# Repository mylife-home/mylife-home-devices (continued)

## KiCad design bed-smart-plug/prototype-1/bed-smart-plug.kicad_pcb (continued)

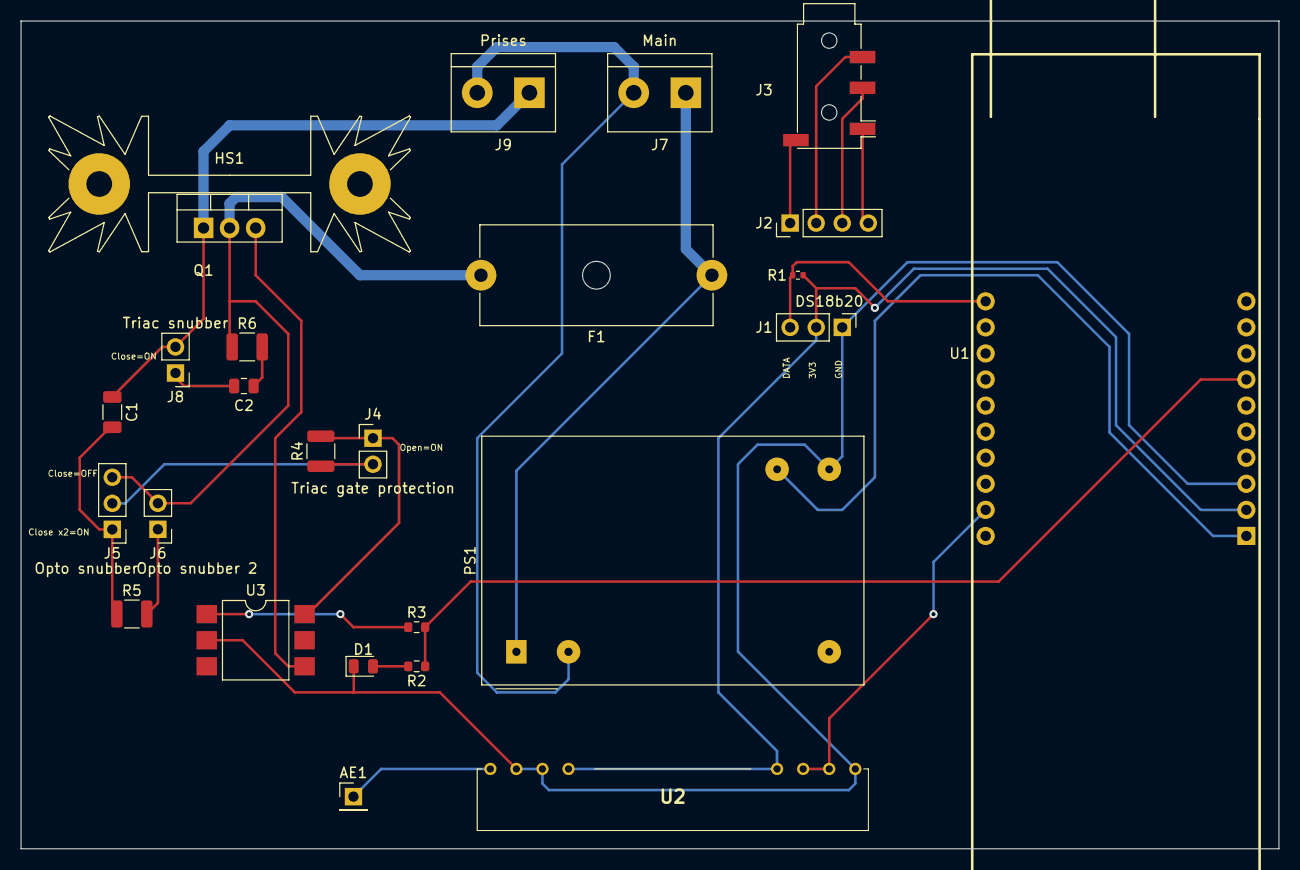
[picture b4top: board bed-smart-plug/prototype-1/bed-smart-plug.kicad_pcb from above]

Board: 2 copper layers, 122.6 x 80.6 mm, 26 parts (0 on the bottom side), 24 nets.

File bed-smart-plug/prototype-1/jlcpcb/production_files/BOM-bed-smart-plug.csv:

Comment,Designator,Footprint,LCSC
10nF/400V,C2,C_0805_2012Metric,C106840
MOC3021M,U3,SMDIP-6_W9.53mm,C108500
220Ω,"R2,R3",R_0603_1608Metric,C22962
LED,D1,D_0805_2012Metric,C2297
4.7KΩ,R1,R_0402_1005Metric,C25900
360Ω/0.5W,R4,R_1210_3225Metric,C2759574
47nF/400V,C1,C_1206_3216Metric,C309031
39Ω/0.5W,R6,R_1210_3225Metric,C422307
3.5mm headphone jack,J3,Jack_3.5mm_PJ320D_Horizontal,C521460
470Ω/0.5W,R5,R_1210_3225Metric,C830186
Conn_01x02_Male,J2,PinHeader_1x04_P2.54mm_Vertical,
Prises,J9,TerminalBlock_bornier-2_P5.08mm,
Triac snubber,J8,PinHeader_1x02_P2.54mm_Vertical,
AM-RX12A-433P,U2,AMRX12A433P,
Opto snubber 2,J6,PinHeader_1x02_P2.54mm_Vertical,
Antenna,AE1,PinHeader_1x01_P2.54mm_Vertical,
Heatsink,HS1,Heatsink_Fischer_SK104-STC-STIC_35x13mm_2xDrill2.5mm,
DS18b20,J1,PinHeader_1x03_P2.54mm_Vertical,
Alim RS PRO 5V 1A,PS1,Converter_ACDC_MeanWell_IRM-03-xx_THT,
ESP32-POE,U1,ESP32-POE,
BT136-600E,Q1,TO-220-3_Vertical,
Opto snubber,J5,PinHeader_1x03_P2.54mm_Vertical,
3A,F1,Fuseholder_Cylinder-5x20mm_Schurter_0031_8201_Horizontal_Open,
Triac gate protection,J4,PinHeader_1x02_P2.54mm_Vertical,
Main,J7,TerminalBlock_bornier-2_P5.08mm,

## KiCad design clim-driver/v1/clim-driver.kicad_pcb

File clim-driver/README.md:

# Clim driver

## Besoin

- Wifi
- doit tenir dans le boitier de clim directement
- alimenté par la clim
- le plus de contrôle possible
- ajouter un capteur de température

### Info clim

- RDC: Toshiba air conditioner RAS-13BKV-E1
- R1: 4x Toshiba air conditioner RAS-05BKV-E
- Telecommande : Toshiba WH-UA01NE
- place derriere capot : 70x15x25
- place pompe relevage :
  - https://www.manomano.fr/p/pompe-relevage-climatisation-mini-orange-230v-aspen-3124579
  - 39x34x80, prévoir sortie cable dans facade 39x34

## Design

- IR send/recv :
  - https://www.wemos.cc/en/latest/_static/files/sch_ir_v1.0.0.pdf
  - https://www.wemos.cc/en/latest/d1_mini_shield/ir.html
  - Led IR: https://fr.rs-online.com/web/p/leds-infrarouges/6997708
  - 18ohm @ 3.3v
- Temp : DS18B2 :
  - en dehors du boitier sinon la temp sera faussée avec la chaleur de l'ESP8266
- Wemos D1 mini :
  - https://www.amazon.fr/dp/B093G72SHN
  - 34x26
- Alim :
  - alim 220v -> 5V 1A : https://fr.rs-online.com/web/p/alimentations-a-decoupage/1812200
  - 37 x 24.5 x 18
  - apparemment il n'existe pas plus petit
- Boitier :
  - https://fr.rs-online.com/web/p/boitiers-pour-usage-general/9190373

## V1

### Wiring

### 3D view

### Main

### Images

| | | |
|---|---|---|
||||
||||

#### CH1

_(pas d'image)_

#### CH2

| | | |
|---|---|---|
||||

#### CH3

| | | |
|---|---|---|
||||

#### CHP

_(pas d'image)_

#### RDC

| | | |
|---|---|---|
||||

### Notes

- Sertissage Dupont : dénuder sur 5mm et ne sertir que le fil conducteur pas la gaine
- Agrandir le trou du boitier à la perceuse à colonne avant de mettre le pas de vis
- Couleurs cable led
  - blanc = +
  - bleu = -
- Couleurs cable DS18B20
  - jaune = IN
  - rouge = 3V3
  - noir = GND

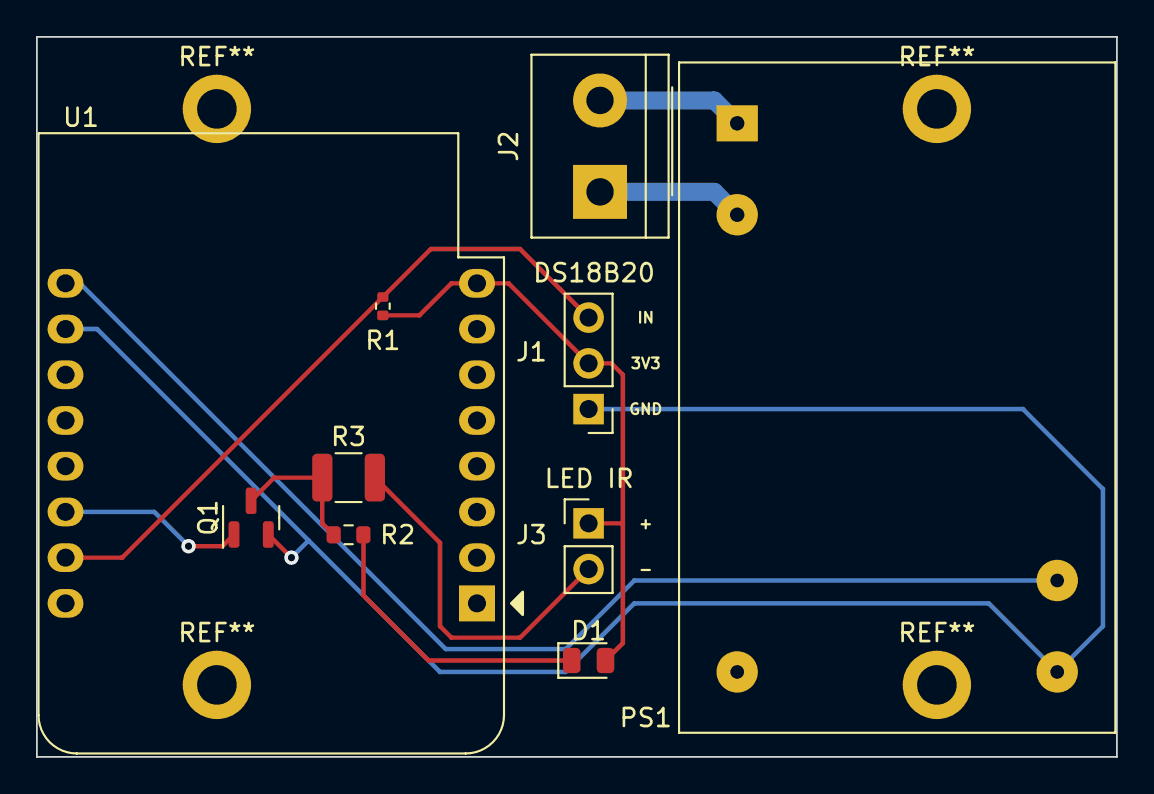
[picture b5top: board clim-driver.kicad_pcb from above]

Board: 2 copper layers, 60.0 x 40.0 mm, 10 parts (0 on the bottom side), 10 nets.

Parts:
D1: LED; D_0805_2012Metric
J1: Conn_01x03_Male; PinHeader_1x03_P2.54mm_Vertical
J2: Screw_Terminal_01x02; TerminalBlock_bornier-2_P5.08mm
J3: Conn_01x02_Pin; PinHeader_1x02_P2.54mm_Vertical
PS1: Alim RS PRO 5V 1A; Converter_ACDC_MeanWell_IRM-03-xx_THT
Q1: BSS138; SOT-23
R1: 4.7KΩ; R_0402_1005Metric
R2: 1KΩ; R_0603_1608Metric
R3: 18Ω/0.5W; R_1210_3225Metric
U1: WeMos_D1_mini; WEMOS_D1_mini_light

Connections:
+3V3: D1.2 (A), J1.2, J3.1, R1.1, U1.8 (3V3)
+5V: PS1.16 (+Vo), U1.9 (5V)
GND: J1.1, PS1.14 (-Vo), Q1.2 (S), U1.10 (GND)
LINE: J2.2, PS1.1 (AC/L)
NEUT: J2.1, PS1.3 (AC/N)
unnamed: D1.1 (K), R2.2
unnamed: J1.3, R1.2, U1.15 (RX)
unnamed: J3.2, R3.2
unnamed: Q1.3 (D), R2.1, R3.1
unnamed: Q1.1 (G), U1.14 (SCL/D1)

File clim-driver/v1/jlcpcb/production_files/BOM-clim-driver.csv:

Comment,Designator,Footprint,LCSC
1KΩ,R2,R_0603_1608Metric,C21190
LED,D1,D_0805_2012Metric,C2297
4.7KΩ,R1,R_0402_1005Metric,C25900
BSS138,Q1,SOT-23,C2938375
18Ω/0.5W,R3,R_1210_3225Metric,C333138
Conn_01x03_Male,J1,PinHeader_1x03_P2.54mm_Vertical,
Screw_Terminal_01x02,J2,TerminalBlock_bornier-2_P5.08mm,
WeMos_D1_mini,U1,WEMOS_D1_mini_light,
Conn_01x02_Pin,J3,PinHeader_1x02_P2.54mm_Vertical,
Alim RS PRO 5V 1A,PS1,Converter_ACDC_MeanWell_IRM-03-xx_THT,

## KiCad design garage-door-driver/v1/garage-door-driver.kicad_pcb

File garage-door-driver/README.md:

# Garage door driver

## Besoin

- doit tenir dans le boitier de la porte ou a côté avec un cable de commande qui sort du boitier
- Wifi
- alimenté par l'alim de la porte
- le plus de contrôle possible
- ajouter un capteur de température

### Fonctionnement de la porte

- Documentation:
  https://www.tubauto.fr/app/uploads/2018/02/procom7-3-fr.pdf

- Moteur garage:

| | | |
|---|---|---|
||||
||||

- Notes:
  - 4 borniers à gauche (comme matériel HiFi)
    - 2 à gauche : alimentation 13V
    - 2 à droite : poussoir déclencheur externe (24v)
  - 2 borniers noirs
    - Sortie (relais d'option) (24v)
      réglage DIL A=OFF B=ON => fin de course (signal ON si porte fermée, OFF sinon)
  - 4 borniers à droite
    - de gauche à droite : 20 - 21 - 5 - 23
    - 20 commun
    - 21-20 => poussoir ouverture totale (4.8v)
    - 5-20 alimentation 24v
    - 23-20 => poussoir ouverture partielle (4.8v)
  - Alimentation moteur:
    - +24v quand montée
    - -24v quand descente

## Design

- Board
  - Wemos D1 mini (ESP8266) 
  - https://amzn.eu/d/irlLEVS
- Alim
  - connexion au 24v
  - https://fr.rs-online.com/web/p/regulateurs-a-decoupage/1934004
  - regarder datasheet pour condensateurs à rajouter
- Borniers
  - https://fr.rs-online.com/web/p/borniers-pour-circuits-imprimes/7901098
- outputs x2 (ouverture partielle/totale)
  - 4.8v vers un commun qui semble etre GND, semble parfait pour sortie transistor
  - 4n35 (1.3v 10ma) https://fr.farnell.com/vishay/4n35/optocoupleur-phototransistor-5000vrms/dp/1328375
  - GPIO 3.3v => R=220ohm
- inputs x3 (moteur double sens, relais d'option)
  - 24v
  - 4n35 (1.3v 10ma) https://fr.farnell.com/vishay/4n35/optocoupleur-phototransistor-5000vrms/dp/1328375
  - 24v => R=2.2kohm
- fixation/layout PCB
  - PCB avec pin header (1 pin sur 2 pour pas de 5.08)
  - les pins headers sont serrés dans les 4 borniers à droite
  - prévoir borniers + fils pour les 2 borniers du milieu
  - taille
    - pin headers vers bord 2.54mm
    - pin headers vers dégagement 1.5cm
    - bord droit retrait degradé sur 1 cm
    - Épaisseur PCB ok des 2 côtés (hauteur/profondeur)
    - H totale = 5cm
    - L totale = 9.5cm

## V1

### Wiring

- GPIO14 - D5 : in moteur (active low)
- GPIO12 - D6 : in moteur (active low)
- GPIO13 - D7 : in porte fermée (active low)
- GPIO4 - D2 : out ouverture partielle
- GPIO5 - D1 : out ouverture totale
- GPIO3 - RX : DS18B20

### 3D view

### Main

### Images

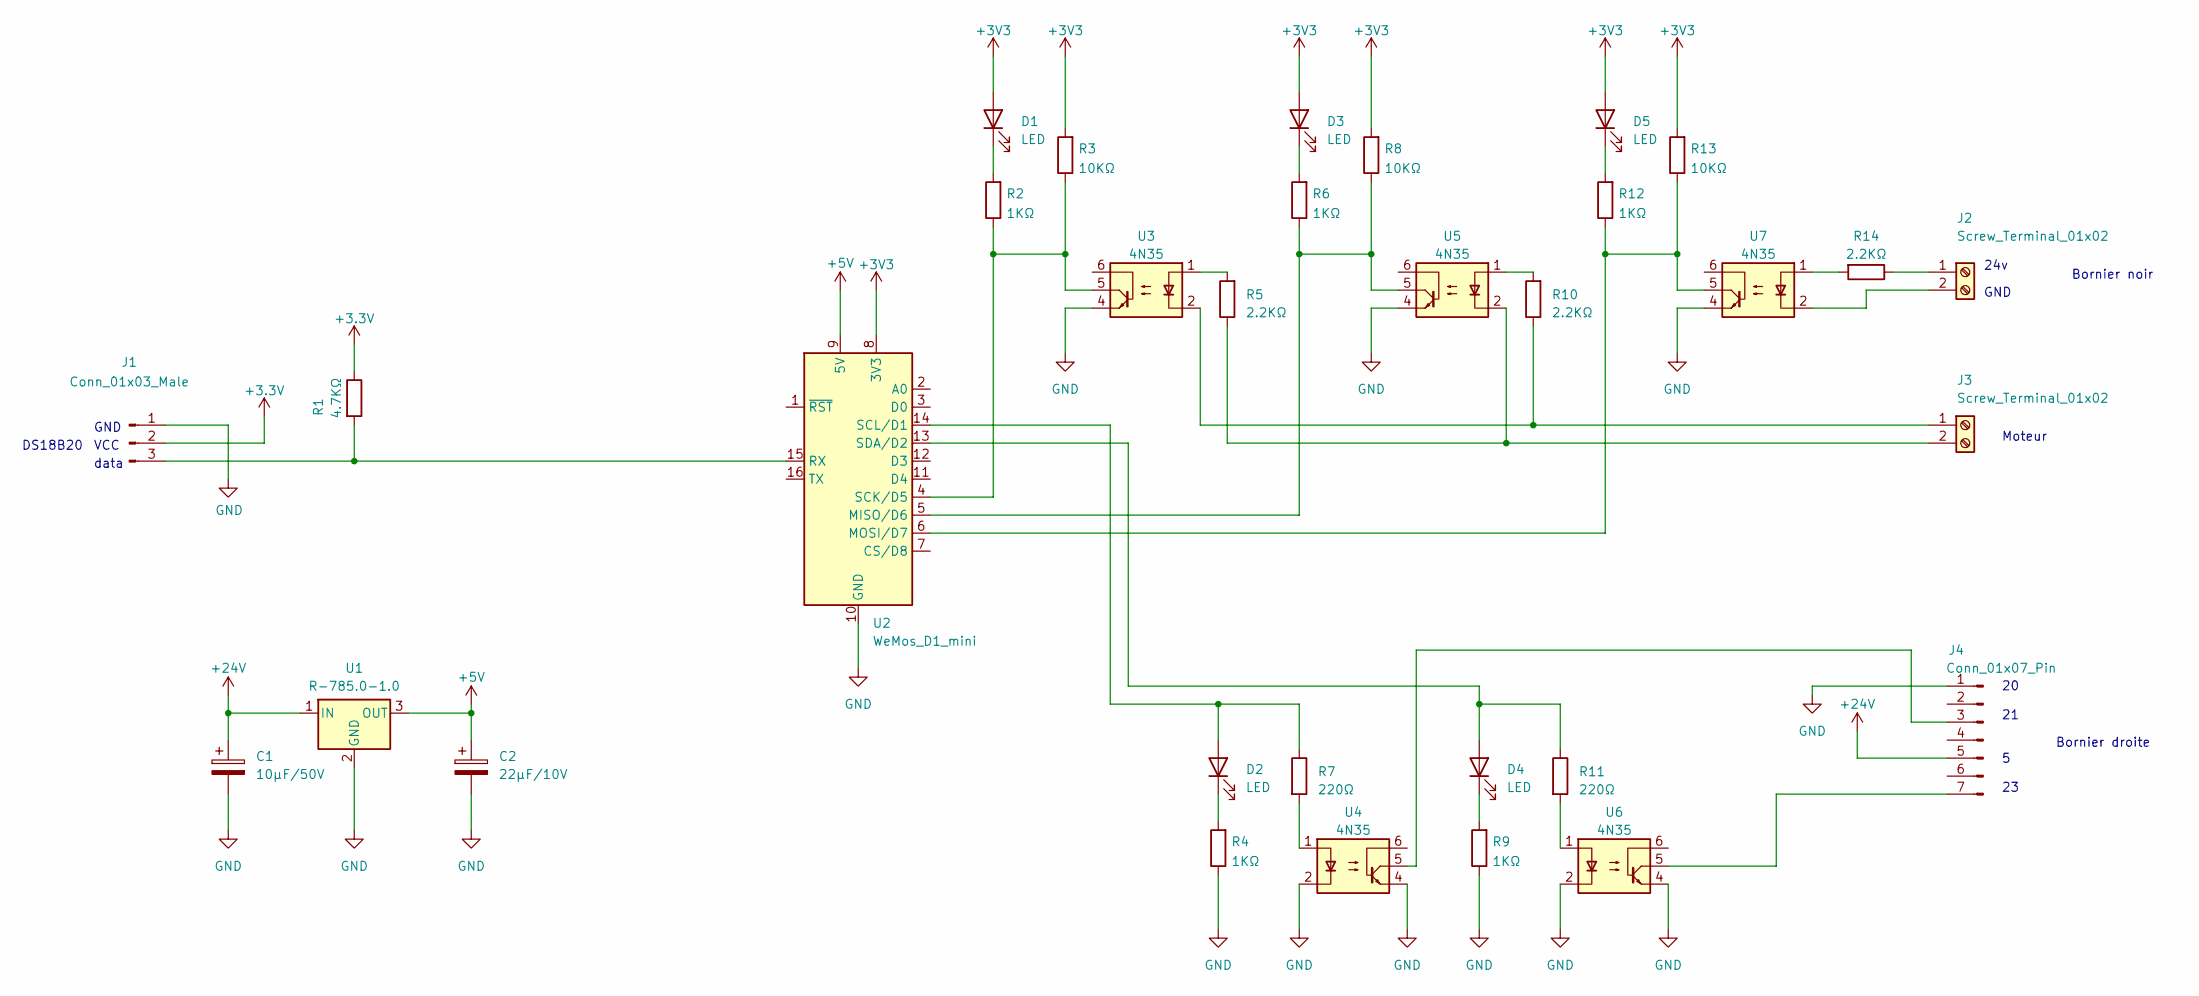
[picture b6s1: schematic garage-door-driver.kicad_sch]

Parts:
C1: 10μF/50V; C_1206_3216Metric; LCSC C417124
C2: 22μF/10V; C_0805_2012Metric; LCSC C92814
D1, D2, D3, D4, D5: LED; D_0805_2012Metric; LCSC C2297
J1: Conn_01x03_Male; PinHeader_1x03_P2.54mm_Vertical
J2, J3: Screw_Terminal_01x02; RS PRO Terminal Small x2
J4: Conn_01x07_Pin; PinHeader_1x07_P2.54mm_Vertical
R1: 4.7KΩ; R_0402_1005Metric; LCSC C25900
R2, R4, R6, R9, R12: 1KΩ; R_0603_1608Metric; LCSC C21190
R3, R8, R13: 10KΩ; R_0603_1608Metric; LCSC C25804
R5, R10, R14: 2.2KΩ; R_0603_1608Metric; LCSC C176136
R7, R11: 220Ω; R_0603_1608Metric; LCSC C22962
U1: R-785.0-1.0; Converter_DCDC_RECOM_R-78E-0.5_THT
U2: WeMos_D1_mini; WEMOS_D1_mini_light
U3, U4, U5, U6, U7: 4N35; DIP-6_W8.89mm_SMDSocket_LongPads; LCSC C500385

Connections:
+5V: C2.1, U1.3 (OUT), U2.9 (5V)
+24V: C1.1, J4.5, U1.1 (IN)
GND: C1.2, C2.2, J1.1, J4.1, R4.1, R9.1, U1.2 (GND), U2.10 (GND), U3.4, U4.2, U4.4, U5.4, U6.2, U6.4, U7.4
unnamed: D1.1 (K), R2.2
unnamed: D2.2 (A), R7.1, U2.14 (SCL/D1)
unnamed: D2.1 (K), R4.2
unnamed: D3.1 (K), R6.2
unnamed: D4.2 (A), R11.1, U2.13 (SDA/D2)
unnamed: D4.1 (K), R9.2
unnamed: D5.1 (K), R12.2
unnamed: J1.3, R1.2, U2.15 (RX)
unnamed: J2.1, R14.1
unnamed: J2.2, U7.2
unnamed: J3.1, R10.1, U3.2
unnamed: J3.2, R5.1, U5.2
unnamed: J4.3, U4.5
unnamed: J4.7, U6.5
unnamed: R5.2, U3.1
unnamed: R7.2, U4.1
unnamed: R10.2, U5.1
unnamed: R11.2, U6.1
unnamed: R14.2, U7.1
unnamed: R6.1, R8.1, U2.5 (MISO/D6), U5.5
unnamed: R12.1, R13.1, U2.6 (MOSI/D7), U7.5
unnamed: R2.1, R3.1, U2.4 (SCK/D5), U3.5

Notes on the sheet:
Bornier droite
20 21 5 23
GND
Bornier noir
24v
data
VCC
Moteur
DS18B20

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
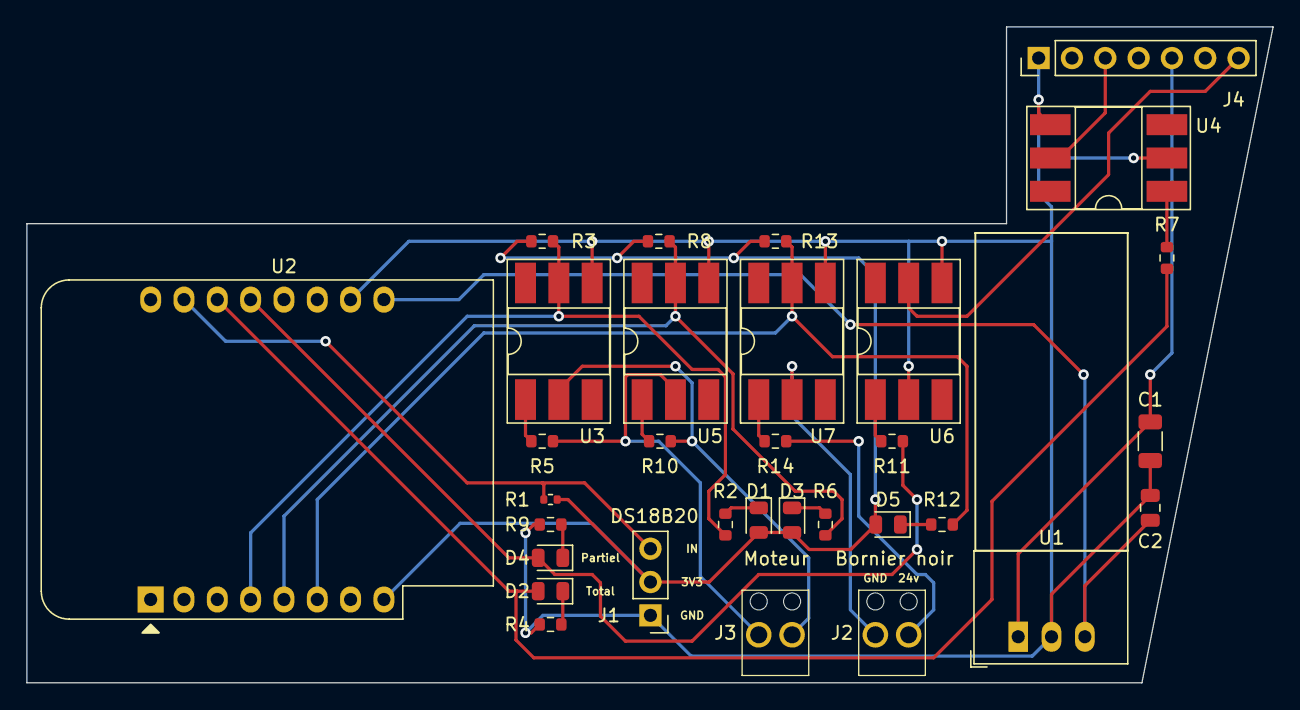
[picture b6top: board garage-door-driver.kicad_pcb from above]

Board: 2 copper layers, 95.0 x 50.0 mm, 32 parts (0 on the bottom side), 26 nets.

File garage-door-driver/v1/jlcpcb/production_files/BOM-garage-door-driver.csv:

Comment,Designator,Footprint,LCSC
2.2KΩ,"R10,R14,R5",R_0603_1608Metric,C176136
1KΩ,"R12,R2,R4,R6,R9",R_0603_1608Metric,C21190
220Ω,"R11,R7",R_0603_1608Metric,C22962
LED,"D1,D2,D3,D4,D5",D_0805_2012Metric,C2297
10KΩ,"R13,R3,R8",R_0603_1608Metric,C25804
4.7KΩ,R1,R_0402_1005Metric,C25900
10μF/50V,C1,C_1206_3216Metric,C417124
4N35,"U3,U4,U5,U6,U7",DIP-6_W8.89mm_SMDSocket_LongPads,C500385
22μF/10V,C2,C_0805_2012Metric,C92814
Conn_01x03_Male,J1,PinHeader_1x03_P2.54mm_Vertical,
WeMos_D1_mini,U2,WEMOS_D1_mini_light,
Conn_01x07_Pin,J4,PinHeader_1x07_P2.54mm_Vertical,
Screw_Terminal_01x02,J2,RS PRO Terminal Small x2,
R-785.0-1.0,U1,Converter_DCDC_RECOM_R-78E-0.5_THT,
Screw_Terminal_01x02,J3,RS PRO Terminal Small x2,

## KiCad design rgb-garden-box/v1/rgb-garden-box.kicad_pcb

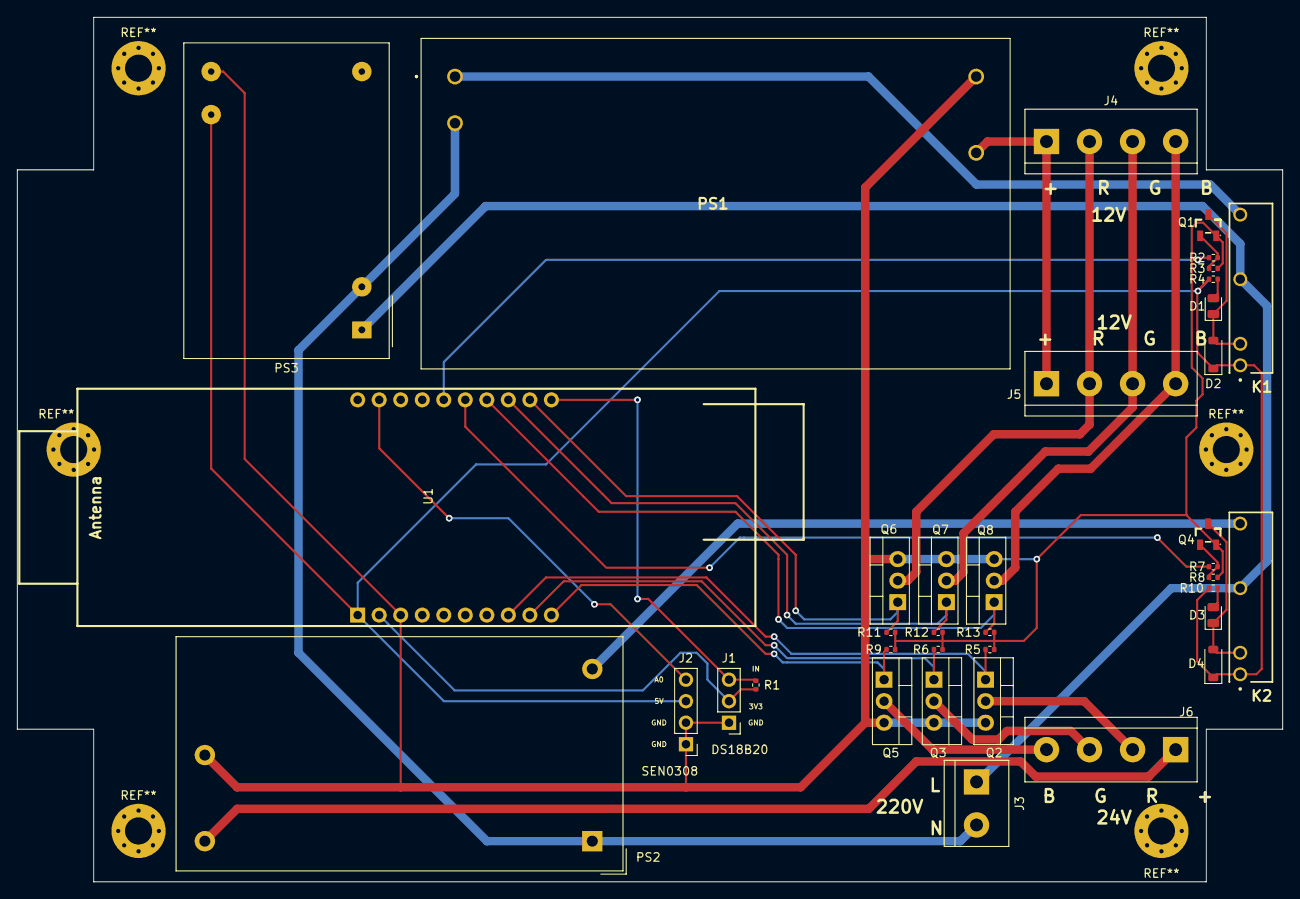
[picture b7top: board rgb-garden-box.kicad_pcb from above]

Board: 2 copper layers, 149.3 x 102.0 mm, 37 parts (0 on the bottom side), 31 nets.

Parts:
D1, D3: LED; D_0805_2012Metric
D2, D4: 1N4148; D_SOD-123
J1: Conn_01x03_Male; PinHeader_1x03_P2.54mm_Vertical
J2: Conn_01x04_Male; PinHeader_1x04_P2.54mm_Vertical
J3: Screw_Terminal_01x02; TerminalBlock_bornier-2_P5.08mm
J4, J5, J6: Screw_Terminal_01x04; TerminalBlock_bornier-4_P5.08mm
K1, K2: G6DN-1A-L_DC5; G6DN-1A-L
PS1: Mean Well 12V 2.5A (30W); IRM-30-12
PS2: RS PRO 24V 833mA (20W); RS PRO Alim 5V 2A
PS3: Alim RS PRO 5V 1A; Converter_ACDC_MeanWell_IRM-03-xx_THT
Q1, Q4: 2N3904; SOT-23-3_L2.9-W1.3-P1.90-LS2.4-TR
Q2, Q3, Q5, Q6, Q7, Q8: IRLZ44N; TO-220-3_Vertical
R1: 4.7KΩ; R_0402_1005Metric
R2, R4, R7, R10: 1KΩ; R_0402_1005Metric
R3, R5, R6, R8, R9, R11, R12, R13: 10KΩ; R_0402_1005Metric
U1: ESP32-POE

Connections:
+3V3: J1.2, R1.1, U1.2 (+3.3V_(out))
+5V: D2.1 (K), D4.1 (K), J2.3, K1.1, K2.1, PS3.16 (+Vo), R4.1, R10.1, U1.1 (+5V)
+12V: J4.1, J5.1, PS1.3 (+Vout)
+24V: J6.1, PS2.4 (+Vo)
GND: J1.1, J2.1, J2.2, PS1.4 (-Vout), PS2.3 (-Vo), PS3.14 (-Vo), Q1.1 (E), Q2.3 (S), Q3.3 (S), Q4.1 (E), Q5.3 (S), Q6.3 (S), Q7.3 (S), Q8.3 (S), R3.2, R5.2, R6.2, R8.2, R9.2, R11.2, R12.2, R13.2, U1.3 (GND)
unnamed: D1.2 (A), R4.2
unnamed: D1.1 (K), D2.2 (A), K1.2, Q1.3 (C)
unnamed: D3.2 (A), R10.2
unnamed: D3.1 (K), D4.2 (A), K2.2, Q4.3 (C)
unnamed: J1.3, R1.2, U1.11 (GPIO13)
unnamed: J2.4, U1.19 (GPIO36)
unnamed: J3.1, K1.5, K2.5, PS3.1 (AC/L)
unnamed: J3.2, PS1.2 (AC/N), PS2.1 (AC/N), PS3.3 (AC/N)
unnamed: J4.2, J5.2, Q6.2 (D)
unnamed: J4.3, J5.3, Q7.2 (D)
unnamed: J4.4, J5.4, Q8.2 (D)
unnamed: J6.2, Q2.2 (D)
unnamed: J6.3, Q3.2 (D)
unnamed: J6.4, Q5.2 (D)
unnamed: K1.8, PS1.1 (AC/L)
unnamed: K2.8, PS2.2 (AC/L)
unnamed: Q1.2 (B), R2.1, R3.1
unnamed: Q2.1 (G), R5.1, U1.8 (GPIO3)
unnamed: Q3.1 (G), R6.1, U1.9 (GPIO4)
unnamed: Q4.2 (B), R7.1, R8.1
unnamed: Q5.1 (G), R9.1, U1.10 (GPIO5)
unnamed: Q6.1 (G), R11.1, U1.12 (GPIO14)
unnamed: Q7.1 (G), R12.1, U1.13 (GPIO15)
unnamed: Q8.1 (G), R13.1, U1.14 (GPIO16)
unnamed: R7.2, U1.15 (GPIO32)
unnamed: R2.2, U1.16 (GPIO33)

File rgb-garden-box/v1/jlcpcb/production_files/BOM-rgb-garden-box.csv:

Comment,Designator,Footprint,LCSC
1KΩ,"R10,R2,R4,R7",R_0402_1005Metric,C11702
2N3904,"Q1,Q4",SOT-23-3_L2.9-W1.3-P1.90-LS2.4-TR,C18536
LED,"D1,D3",D_0805_2012Metric,C2297
10KΩ,"R11,R12,R13,R3,R5,R6,R8,R9",R_0402_1005Metric,C25744
4.7KΩ,R1,R_0402_1005Metric,C25900
1N4148,"D2,D4",D_SOD-123,C81598
IRLZ44N,Q8,TO-220-3_Vertical,
IRLZ44N,Q7,TO-220-3_Vertical,
IRLZ44N,Q6,TO-220-3_Vertical,
IRLZ44N,Q5,TO-220-3_Vertical,
IRLZ44N,Q3,TO-220-3_Vertical,
IRLZ44N,Q2,TO-220-3_Vertical,
G6DN-1A-L_DC5,K1,G6DN-1A-L,
Screw_Terminal_01x04,J5,TerminalBlock_bornier-4_P5.08mm,
Screw_Terminal_01x04,J6,TerminalBlock_bornier-4_P5.08mm,
Mean Well 12V 2.5A (30W),PS1,IRM-30-12,
G6DN-1A-L_DC5,K2,G6DN-1A-L,
Conn_01x03_Male,J1,PinHeader_1x03_P2.54mm_Vertical,
Screw_Terminal_01x04,J4,TerminalBlock_bornier-4_P5.08mm,
Screw_Terminal_01x02,J3,TerminalBlock_bornier-2_P5.08mm,
RS PRO 24V 833mA (20W),PS2,RS PRO Alim 5V 2A,
ESP32-POE,U1,ESP32-POE,
Alim RS PRO 5V 1A,PS3,Converter_ACDC_MeanWell_IRM-03-xx_THT,
Conn_01x04_Male,J2,PinHeader_1x04_P2.54mm_Vertical,

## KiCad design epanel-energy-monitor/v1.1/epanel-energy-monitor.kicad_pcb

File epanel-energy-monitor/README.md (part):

# ePanel Energy Monitor

## Besoin

- 12 capteurs
  - abonnement 12KVA ~ 55A
  - 4 sur inter diff (entre 40A et 63A)
  - 8 sur disjoncteurs (entre 10A et 32A)
- teleinfo

## Design

- MCP3208 x2
- déplacer ESP dans un boitier DIN a part

### Matériel

- Boîtier : 
  - https://fr.rs-online.com/web/p/boitiers-rail-din/7495837
  - https://fr.farnell.com/camdenboss/cnmb-6-kit/boitier-rail-din-m6/dp/3954259
- Borniers :
  - Petits : https://fr.rs-online.com/web/p/borniers-pour-circuits-imprimes/7901098
  - Grands : https://fr.rs-online.com/web/p/borniers-pour-circuits-imprimes/1444286
- Selecteurs : 
  - https://fr.rs-online.com/web/p/interrupteurs-dip-de-codage-rotatif/1796751
  - https://fr.farnell.com/nidec-copal/ss-10-15spe/commut-rotatif-sp5t-0-1a-5vdc/dp/2854806
- Câble 2x4 : https://www.amazon.fr/sourcing-map-Connecteur-Broche-Femelle/dp/B07H26VF1J
- Transfo : https://fr.rs-online.com/web/p/transformateurs-pour-circuits-imprimes/7320525
-  CT Clamp Schneider:
  - https://www.amazon.fr/Transformateurs-courant-ferm%C3%A9s-80a-Lot/dp/B01G5M1MT4
  - https://www.se.com/fr/fr/product/EER39200/wiser-energy-lot-de-5-tc-transformateurs-de-courant-ferm%C3%A9s-80a/

## V1.1

### Réglages

- pos1 = 220Ω = 10A
- pos2 = 120Ω = 16A
- pos3 = 100Ω = 20A
- pos4 =  62Ω = 32A
- pos5 =  33Ω = 60A

### 3D view

### Main

### CT Sensor

### Images

| | | |
|---|---|---|
||||
||||
||||

### Notes:

- plus de résistances 200Ω en stock, donc remplacement par une 220Ω. L'intensité max pour 10A pass de 10.5 à 9.5

## V1

### Réglages

- pos1 = 200Ω = 10A
- pos2 = 120Ω = 16A
- pos3 = 100Ω = 20A
- pos4 =  62Ω = 32A
- pos5 =  33Ω = 60A

### 3D view

### Main

### CT Sensor

### TODO

- OK LTV-814 : mauvais footprint, le bon est plus "écarté", cf jlcpcb/parts
- OK BSS138: mauvais pinout/footprint, cf jlcpcb/parts
- OK borniers pour CT plus petits (2.54 ecartement) -> https://fr.rs-online.com/web/p/borniers-pour-circuits-imprimes/7901098
- OK transfo: pastilles bien placées mais trop petites
- OK transfo: ajouter des pin headers sur secondaire pour facilement pouvoir mesurer la tension au voltmetre
- OK Au lieu de jumpers pour config resistances, mettre un commutateur rotatif :
  - https://fr.rs-online.com/web/p/interrupteurs-dip-de-codage-rotatif/1796751
  - https://fr.farnell.com/nidec-copal/ss-10-15spe/commut-rotatif-sp5t-0-1a-5vdc/dp/2854806
- Note: Boitier DIN : Largeur espace pour bornier : 1.3cm
- OK ajouter une led pour montrer qu'il est bien alimenté

### Bugs

- pinout SS-10 KO !!!
```
1 pos3       5 NC
2 pos2       6 C
3 C          7 pos5
4 pos1       8 pos4
```
Note: le point correspond à l'angle rogné sur le SS-10

- pinout bornier inversé : les trous sont du côté des cables

## Prototype-1

### Tests

### Observations

- Teleinfo
  - mauvais composant pour optocoupleur :
    - courant LTV-8141
    - correct: LTV-814 (C125118)
  - voir si on doit mettre une résistance de 4.7K, 1.2K ou 1K
- CT Clamp
  - les prises jack a souder sont très peu épaisses, elles doivent être au board du PCB ou changer de modèle
  - test avec aspirateur:
    - Théoriquement: 1300W /230V = 5.6A
    - Mesure avec ampèremètre sur directement sur le courant secteur : 6.12A
    - Mesure avec voltmètre aux bornes du burden resistor 120ohm : 0.31V /120Rb *2000 = 5.16A
    - Mesure avec oem_clamp recodé : 7.55A à l'allumage puis 6.35A après (instable). Note : le 0 est à 0.06A

### A faire pour proto 2:

- TIC
  - LTV-814
  - plusieurs choix de résistances pour TIC : 1k, 1.2k, 2k, 3.3k, 4.7k
  - mettre des pins headers pour pouvoir mesurer a l'oscillo si problème
- CT Clamp
  - mettre un MCP3208
  - jumper pour passer soit par MCP3208 soit direct sur ESP32
  - attention: GPIO2 et GPIO4 ne semble pas etre valides pour ADC avec esphome. GPIO32 et GPIO33 oui
  - mettre des pins headers pour pouvoir mesurer au voltmètre
  - plusieurs burden possibles:
    - 10A 233ohm -> 220 (10.6A)
    - 16A 146ohm -> 150 (15.6A)
    - 20A 117ohm -> 120 (19.4A)
    - 32A 73ohm -> 75 (31.1A)
    - 60A 39ohm -> 33 (70.7A)
- test emplacement ESP32
  - avec le connecteur ethernet vers le bas
  - sur la partie droite, mais pas collé (sinon les ergo vont gener)
  - au milieu en hauteur
  - on decoupera le boitier au dremel pour faire la place pour le connecteur ethernet

## Prototype-2

### Tests

- CT Clamp avec ADC ESP32 - Burden 220ohm (10A) sur sèche cheveux 1500W
  - eteint : 0.030A - 0.036A
  - level1 : 2.321A - 2.323A = 533W
  - level3 : 6.395A - 6.431A = 1470W - 1479W

- CT Clamp avec MCP3008 - Burden 220ohm (10A) sur sèche cheveux 1500W
  - eteint : 0.043A - 0.105A
  - level1 : 2.316A = 532.68W
  - level3 : 6.335A = 1457W

- CT Clamp avec MCP3008 - Burden 75ohm (32A) sur SPA
  - au "repos" : 0.117A - 0.258A -> 26,91W - 59,34W
  - filtration? : 0.551A -> 126,73W
  - au "travail" (chauffage ?) : 11.751A -> 2700W

- CT Clamp comparaison avec Schneider avec MCP3008 - Burden 75ohm sur sèche cheveux 1500W - level3
  - Mesure avec CT clamp YHDC : 6.3 - 6.4
  - Mesure avec multimetre : 6.36
  - Mesure schneider config 1600 turns => 5.6
  - Mesure schneider config 2000 turns => 7
  => en faisant le ratio, CT clamp Schneider = 1800 turns

- CT Clamp comparaison avec Schneider avec MCP3008 - Burden 75ohm sur ampoule 40W
  - Mesure schneider config 1800 turns : 0.27
  - Mesure schneider config 1600 turns : 0.24
  - Mesure avec multimetre : 0.15
  - 40W = 0.17
  => en faisant le ratio, CT clamp Shneider = 1000 turns => tres peut precis, mais 0.27A sur 32A < 1%

- CT Clamp comparaison avec Schneider avec MCP3008 - Burden 220ohm sur ampoule 40W
  - Mesure schneider config 1800 turns : 0.18
  - Mesure avec multimetre : 0.15
  - 40W = 0.17

### Observations

- Teleinfo
  - ne fonctionne pas
  - WeMos TIC fonctionne, schematic : https://cdn.tindiemedia.com/images/resize/s_ZnNZRPrxDSvn3I8rBo9nkt9-8=/p/fit-in/1370x912/filters:fill(fff)/i/5857/products/2021-11-24T17%3A07%3A47.675Z-WeMos-TIC-sch.png?1637747448
  - Note : les valeurs des resistances correspondent bien au schematic
- CT Clamp MCP3008
  - GPIO15 = strapping pin
  - rajouter Voltage sensor pour pouvoir calculer la puissance réelle
    - https://learn.openenergymonitor.org/electricity-monitoring/voltage-sensing/measuring-voltage-with-an-acac-power-adapter
    - https://fr.rs-online.com/web/p/transformateurs-pour-circuits-imprimes/1213819
  - tester reactivité ESP32 avec 16 mesures (meme si pas de CT clamp, juste pour etre sur que ca ne perde pas en reactivite)
  - trouver des CT Clamp plus petits ? comme ceux de Schneider ?
    - ceux de Schneider:
      - https://www.amazon.fr/Transformateurs-courant-ferm%C3%A9s-80a-Lot/dp/B01G5M1MT4
      - https://www.se.com/fr/fr/product/EER39200/wiser-energy-lot-de-5-tc-transformateurs-de-courant-ferm%C3%A9s-80a/
      - semble etre 80A:50mA => en fait 1800 turns
      - tore d'une seule pièce
  - faire une sortie screwterminal a cote du jack pour pouvoir tester d'autres CT Clamp
  - burdens:
    - essayer d'optimiser les valeurs en pouvant les mettre en //
    - attention : schneider CT turns = 1800, YHDC CT turns = 2000
- Montage ESP32 dans DIN box
  - trop sur le côté, décaler de 2-3mm vers le milieu
  - la prochaine fois faire un truc moins cochon au Dremel
- Montage prises Jack
  - l'emplacement est parfait, mais on ne peut pas en mettre de chaque coté de la board et la faire rentrer dans le boitiers car ils depassent

### A faire pour proto 3

- Teleinfo
  - doit fonctionner
  - ajouter une led
- CT Clamp
  - ajouter un ADS1115 pour tester la difference de précision, avec un autre switch
    - datasheet : https://www.ti.com/lit/ds/symlink/ads1115.pdf
    - avec un burden pour 60A et la precision de l'ADC, cela suffit peut etre sans burden en plus ?
  - ajouter capteur de tension
    - Transfo : 6V -> https://fr.rs-online.com/web/p/transformateurs-pour-circuits-imprimes/7320525
    - no load voltage = x1.8 => 10.8V RMS
    - https://learn.openenergymonitor.org/electricity-monitoring/voltage-sensing/measuring-voltage-with-an-acac-power-adapter
    - 10.8V RMS
    - = 15.3V peak
    - = 30,6V peak-peak
    - ratio: 12 / (100 + 12) = 0,107
    - = 3.274V peak-peak
  - ajouter ampli op
    - https://learn.openenergymonitor.org/electricity-monitoring/ctac/acac-buffered-voltage-bias
    - pour chaque capteur, switch ampli op ou pont diviseur
  - mettre plusieurs capteurs de courant pour etre sur que l'ampli op fonctionne pour plusieurs, eg : 3 capteurs CT + 1 tension
  - mettre des terminalscrews au lieu des jacks pour tester CT Schneider
  - jeu de burden resistances pour CT turns 1800
    - 10A 210ohm -> 200 (10.5A)
    - 16A 131ohm -> 130 (16.2A)
    - 20A 105ohm -> 100 (21A)
    - 32A 66ohm -> 62 (33.9A)
    - 60A 35ohm -> 33 (63.6A)
  - tester avec vraie alim (pour tester la stabilité des mesures avec l'alim)
  - diodes pour protéger les ADC : https://openenergymonitor.github.io/forum-archive/sites/default/files/MyInputCircuits_0.jpg
    - ADS a deja des protections dans son MUX
  - pour chaque capteur, switch ADS vs MCP vs ESP
- Montage ESP32
  - corriger l'emplacement sur la board

## Prototype-3

### Tests

- Sortie transfo mesurée :
  - (7.5VRMS)
  - 8.8V RMS

- MCP/OP (seche cheveux sur ct1)

```
[09:39:28][D][oem_computer:065]: 'ct2' - v_rms=234.4V, i_rms=0.052A, p_real=0.3W (sample count: 1025, sample per period: 102.50)
[09:39:28][D][sensor:127]: 'epanel-ct2-current': Sending state 0.05180 A with 2 decimals of accuracy
[09:39:28][D][sensor:127]: 'epanel-ct2-voltage': Sending state 234.41190 V with 0 decimals of accuracy
[09:39:28][D][sensor:127]: 'epanel-ct2-apparent-power': Sending state 12.14348 VA with 0 decimals of accuracy
[09:39:28][D][sensor:127]: 'epanel-ct2-real-power': Sending state 0.34598 W with 0 decimals of accuracy
[09:39:29][D][oem_computer:065]: 'ct1' - v_rms=234.9V, i_rms=5.399A, p_real=-989.3W (sample count: 1046, sample per period: 104.60)
[09:39:29][D][sensor:127]: 'epanel-ct1-current': Sending state 5.39941 A with 2 decimals of accuracy
[09:39:29][D][sensor:127]: 'epanel-ct1-voltage': Sending state 234.88547 V with 0 decimals of accuracy
[09:39:29][D][sensor:127]: 'epanel-ct1-apparent-power': Sending state 1268.24182 VA with 0 decimals of accuracy
[09:39:29][D][sensor:127]: 'epanel-ct1-real-power': Sending state -989.25970 W with 0 decimals of accuracy
[09:39:30][D][oem_computer:065]: 'ct3' - v_rms=235.3V, i_rms=0.050A, p_real=0.0W (sample count: 1055, sample per period: 105.50)
[09:39:30][D][sensor:127]: 'epanel-ct3-current': Sending state 0.04952 A with 2 decimals of accuracy
[09:39:30][D][sensor:127]: 'epanel-ct3-voltage': Sending state 235.33501 V with 0 decimals of accuracy
[09:39:30][D][sensor:127]: 'epanel-ct3-apparent-power': Sending state 11.65409 VA with 0 decimals of accuracy
[09:39:30][D][sensor:127]: 'epanel-ct3-real-power': Sending state 0.02975 W with 0 decimals of accuracy

[09:39:38][D][oem_computer:065]: 'ct2' - v_rms=234.8V, i_rms=0.047A, p_real=0.5W (sample count: 1032, sample per period: 103.20)
[09:39:38][D][sensor:127]: 'epanel-ct2-current': Sending state 0.04736 A with 2 decimals of accuracy
[09:39:38][D][sensor:127]: 'epanel-ct2-voltage': Sending state 234.82834 V with 0 decimals of accuracy
[09:39:38][D][sensor:127]: 'epanel-ct2-apparent-power': Sending state 11.12200 VA with 0 decimals of accuracy
[09:39:38][D][sensor:127]: 'epanel-ct2-real-power': Sending state 0.52791 W with 0 decimals of accuracy
[09:39:39][D][oem_computer:065]: 'ct1' - v_rms=235.0V, i_rms=5.385A, p_real=-987.9W (sample count: 1054, sample per period: 105.40)
[09:39:39][D][sensor:127]: 'epanel-ct1-current': Sending state 5.38487 A with 2 decimals of accuracy
[09:39:39][D][sensor:127]: 'epanel-ct1-voltage': Sending state 235.02916 V with 0 decimals of accuracy
[09:39:39][D][sensor:127]: 'epanel-ct1-apparent-power': Sending state 1265.60107 VA with 0 decimals of accuracy
[09:39:39][D][sensor:127]: 'epanel-ct1-real-power': Sending state -987.94031 W with 0 decimals of accuracy
[09:39:40][D][oem_computer:065]: 'ct3' - v_rms=234.7V, i_rms=0.046A, p_real=0.4W (sample count: 1048, sample per period: 104.80)
[09:39:40][D][sensor:127]: 'epanel-ct3-current': Sending state 0.04584 A with 2 decimals of accuracy
[09:39:40][D][sensor:127]: 'epanel-ct3-voltage': Sending state 234.70300 V with 0 decimals of accuracy
[09:39:40][D][sensor:127]: 'epanel-ct3-apparent-power': Sending state 10.75784 VA with 0 decimals of accuracy
[09:39:40][D][sensor:127]: 'epanel-ct3-real-power': Sending state 0.44836 W with 0 decimals of accuracy
```

v_rms stddev: (234.4, 234.9, 235.3, 234.8, 235.0, 234.7) -> 0.27537852736431

- MCP/DIV (seche cheveux sur ct1)

```
[09:41:57][D][oem_computer:065]: 'ct3' - v_rms=236.3V, i_rms=0.087A, p_real=0.7W (sample count: 791, sample per period: 79.10)
[09:41:57][D][sensor:127]: 'epanel-ct3-current': Sending state 0.08679 A with 2 decimals of accuracy
[09:41:57][D][sensor:127]: 'epanel-ct3-voltage': Sending state 236.31416 V with 0 decimals of accuracy
[09:41:57][D][sensor:127]: 'epanel-ct3-apparent-power': Sending state 20.50956 VA with 0 decimals of accuracy
[09:41:57][D][sensor:127]: 'epanel-ct3-real-power': Sending state 0.68594 W with 0 decimals of accuracy
[09:41:57][D][oem_computer:065]: 'ct1' - v_rms=236.9V, i_rms=5.411A, p_real=-1009.7W (sample count: 518, sample per period: 51.80)
[09:41:57][D][sensor:127]: 'epanel-ct1-current': Sending state 5.41132 A with 2 decimals of accuracy
[09:41:57][D][sensor:127]: 'epanel-ct1-voltage': Sending state 236.94221 V with 0 decimals of accuracy
[09:41:57][D][sensor:127]: 'epanel-ct1-apparent-power': Sending state 1282.17102 VA with 0 decimals of accuracy
[09:41:57][D][sensor:127]: 'epanel-ct1-real-power': Sending state -1009.70721 W with 0 decimals of accuracy
[09:41:59][D][oem_computer:065]: 'ct2' - v_rms=236.1V, i_rms=0.072A, p_real=1.1W (sample count: 1054, sample per period: 105.40)
[09:41:59][D][sensor:127]: 'epanel-ct2-current': Sending state 0.07230 A with 2 decimals of accuracy
[09:41:59][D][sensor:127]: 'epanel-ct2-voltage': Sending state 236.13994 V with 0 decimals of accuracy
[09:41:59][D][sensor:127]: 'epanel-ct2-apparent-power': Sending state 17.07363 VA with 0 decimals of accuracy
[09:41:59][D][sensor:127]: 'epanel-ct2-real-power': Sending state 1.05915 W with 0 decimals of accuracy

[09:42:07][D][oem_computer:065]: 'ct3' - v_rms=236.5V, i_rms=0.103A, p_real=1.8W (sample count: 797, sample per period: 79.70)
[09:42:07][D][sensor:127]: 'epanel-ct3-current': Sending state 0.10278 A with 2 decimals of accuracy
[09:42:07][D][sensor:127]: 'epanel-ct3-voltage': Sending state 236.46739 V with 0 decimals of accuracy
[09:42:07][D][sensor:127]: 'epanel-ct3-apparent-power': Sending state 24.30380 VA with 0 decimals of accuracy
[09:42:07][D][sensor:127]: 'epanel-ct3-real-power': Sending state 1.82878 W with 0 decimals of accuracy
[09:42:07][D][oem_computer:065]: 'ct1' - v_rms=235.3V, i_rms=5.455A, p_real=-1005.7W (sample count: 556, sample per period: 55.60)
[09:42:07][D][sensor:127]: 'epanel-ct1-current': Sending state 5.45496 A with 2 decimals of accuracy
[09:42:07][D][sensor:127]: 'epanel-ct1-voltage': Sending state 235.33839 V with 0 decimals of accuracy
[09:42:07][D][sensor:127]: 'epanel-ct1-apparent-power': Sending state 1283.76111 VA with 0 decimals of accuracy
[09:42:07][D][sensor:127]: 'epanel-ct1-real-power': Sending state -1005.74493 W with 0 decimals of accuracy
[09:42:09][D][oem_computer:065]: 'ct2' - v_rms=236.5V, i_rms=0.076A, p_real=1.9W (sample count: 1054, sample per period: 105.40)
[09:42:09][D][sensor:127]: 'epanel-ct2-current': Sending state 0.07567 A with 2 decimals of accuracy
[09:42:09][D][sensor:127]: 'epanel-ct2-voltage': Sending state 236.53575 V with 0 decimals of accuracy
[09:42:09][D][sensor:127]: 'epanel-ct2-apparent-power': Sending state 17.89754 VA with 0 decimals of accuracy
[09:42:09][D][sensor:127]: 'epanel-ct2-real-power': Sending state 1.92734 W with 0 decimals of accuracy
```

v_rms stddev: (236.3, 236.9, 236.1, 236.5, 235.3, 236.5) -> 0.49553562491061

- ADS

  too slow, eg: `(sample count: 34, sample per period: 3.40)` with `continuous_mode: on` and `frequency: 200kHz` (400 and 800 does not work)

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
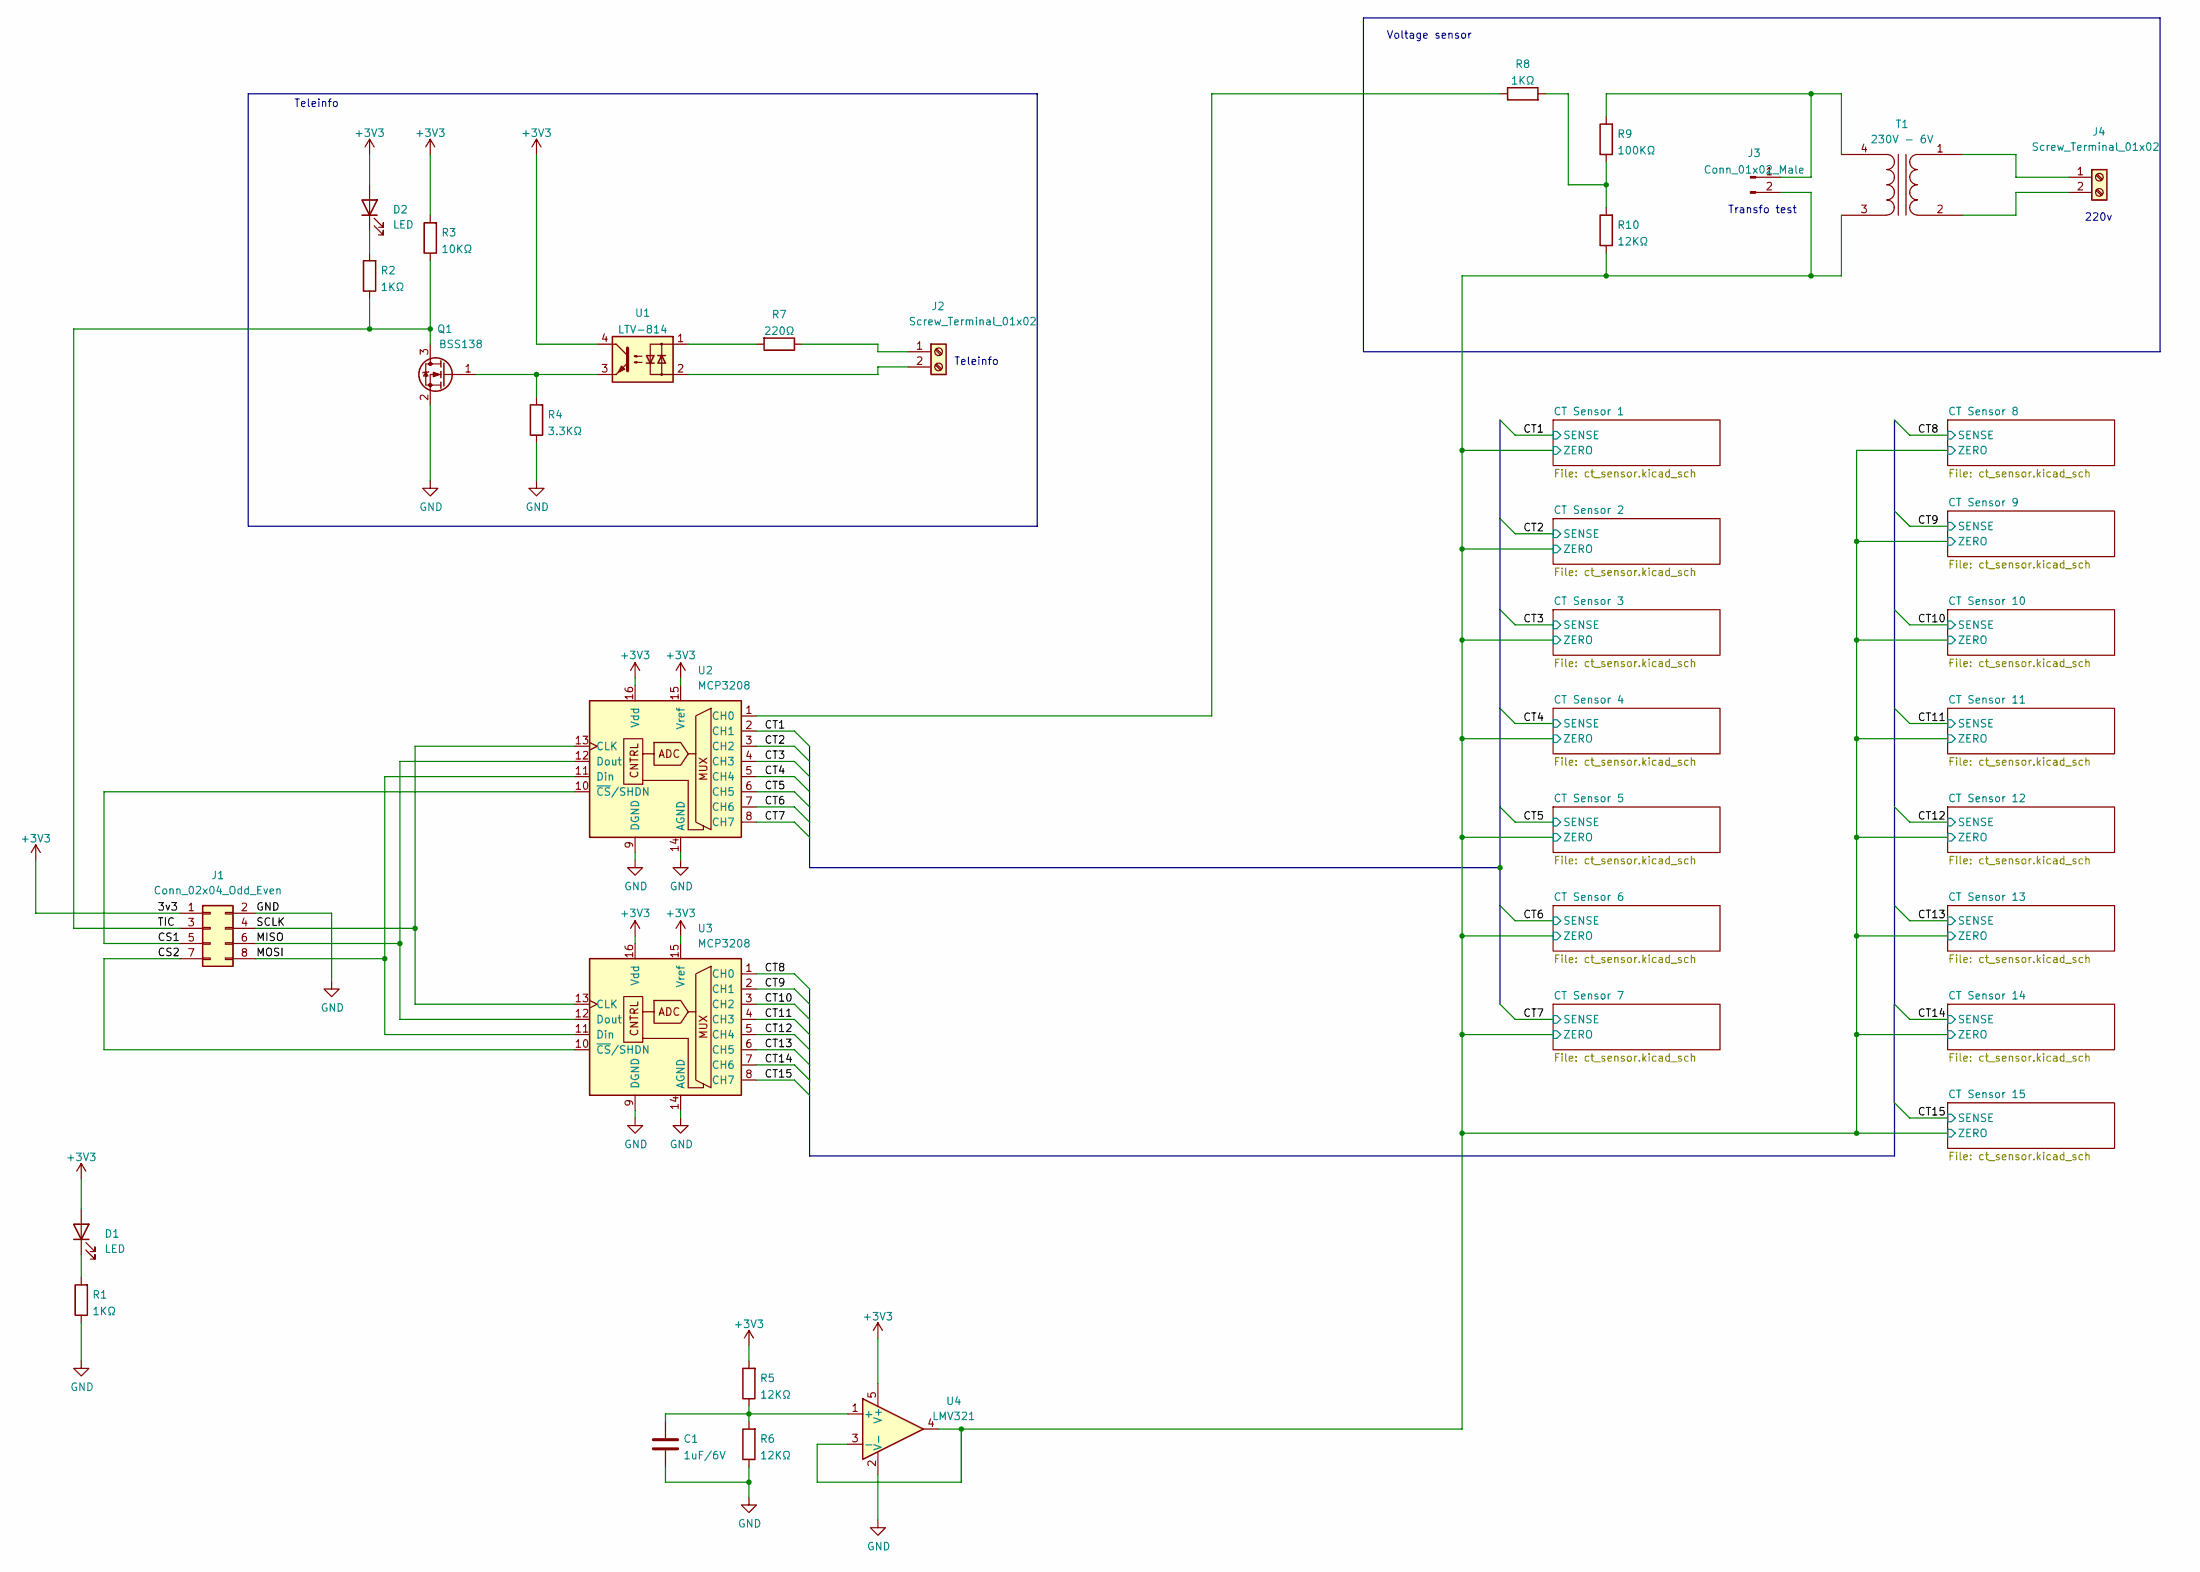
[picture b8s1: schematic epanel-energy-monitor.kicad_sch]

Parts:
C1: 1uF/6V; R_0603_1608Metric; LCSC C15849
D1, D2: LED; D_0805_2012Metric; LCSC C2297
J1: Conn_02x04_Odd_Even; PinHeader_2x04_P2.54mm_Vertical
J2: Screw_Terminal_01x02; RS PRO Terminal Small x2
J3: Conn_01x02_Male; PinHeader_1x02_P2.54mm_Vertical
J4: Screw_Terminal_01x02; TerminalBlock_bornier-2_P5.08mm
Q1: BSS138; SOT-23; LCSC C2938375
R1, R2, R8: 1KΩ; R_0603_1608Metric; LCSC C21190
R3: 10KΩ; R_0603_1608Metric; LCSC C25804
R4: 3.3KΩ; R_0603_1608Metric; LCSC C22978
R5, R6, R10: 12KΩ; R_0603_1608Metric; LCSC C22790
R7: 220Ω; R_0603_1608Metric; LCSC C22962
R9: 100KΩ; R_0603_1608Metric; LCSC C25803
T1: 230V - 6V; RS PRO Transfo 6V 0.35VA
U1: LTV-814; SMDIP-4_W9.53mm; LCSC C125118
U2, U3: MCP3208; SOIC-16_3.9x9.9mm_P1.27mm; LCSC C16939
U4: LMV321; SOT-23-5; LCSC C7972

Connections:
+3V3: D1.2 (A), D2.2 (A), J1.1, R3.2, R5.2, U1.4, U2.15 (Vref), U2.16 (Vdd), U3.15 (Vref), U3.16 (Vdd), U4.5 (V+)
/CS1: J1.5, U2.10 (~CS/SHDN)
/CS2: J1.7, U3.10 (~CS/SHDN)
/CT1: U2.2 (CH1); also elsewhere on the board
/CT2: U2.3 (CH2); also elsewhere on the board
/CT3: U2.4 (CH3); also elsewhere on the board
/CT4: U2.5 (CH4); also elsewhere on the board
/CT5: U2.6 (CH5); also elsewhere on the board
/CT6: U2.7 (CH6); also elsewhere on the board
/CT7: U2.8 (CH7); also elsewhere on the board
/CT8: U3.1 (CH0); also elsewhere on the board
/CT9: U3.2 (CH1); also elsewhere on the board
/CT10: U3.3 (CH2); also elsewhere on the board
/CT11: U3.4 (CH3); also elsewhere on the board
/CT12: U3.5 (CH4); also elsewhere on the board
/CT13: U3.6 (CH5); also elsewhere on the board
/CT14: U3.7 (CH6); also elsewhere on the board
/CT15: U3.8 (CH7); also elsewhere on the board
/CT Sensor 1/ZERO: J3.2, R10.1, T1.3 (SA), U4.3 (-), U4.4; also elsewhere on the board
/MISO: J1.6, U2.12 (Dout), U3.12 (Dout)
/MOSI: J1.8, U2.11 (Din), U3.11 (Din)
/SCLK: J1.4, U2.13 (CLK), U3.13 (CLK)
/TIC: J1.3, Q1.3 (D), R2.1, R3.1
GND: C1.2, J1.2, Q1.2 (S), R1.1, R4.1, R6.1, U2.9 (DGND), U2.14 (AGND), U3.9 (DGND), U3.14 (AGND), U4.2 (V-)
unnamed: D1.1 (K), R1.2
unnamed: D2.1 (K), R2.2
unnamed: J2.1, R7.1
unnamed: J2.2, U1.2
unnamed: J3.1, R9.2, T1.4 (SB)
unnamed: J4.1, T1.1 (AA)
unnamed: J4.2, T1.2 (AB)
unnamed: Q1.1 (G), R4.2, U1.3
unnamed: R7.2, U1.1
unnamed: R8.2, R9.1, R10.2
unnamed: R8.1, U2.1 (CH0)
unnamed: C1.1, R5.1, R6.2, U4.1 (+)

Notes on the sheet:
Teleinfo
Transfo test
220v
Voltage sensor
